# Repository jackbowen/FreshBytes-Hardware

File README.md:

# FreshBytes Hardware

All of the hardware needed to run FreshBytes, a hydroponic and aquaponic monitoring and control system. The system runs on [this software](https://github.com/jackbowen/FreshBytes-Backend) and is interacted with through [this app](https://github.com/jackbowen/FreshBytes-WebApp).

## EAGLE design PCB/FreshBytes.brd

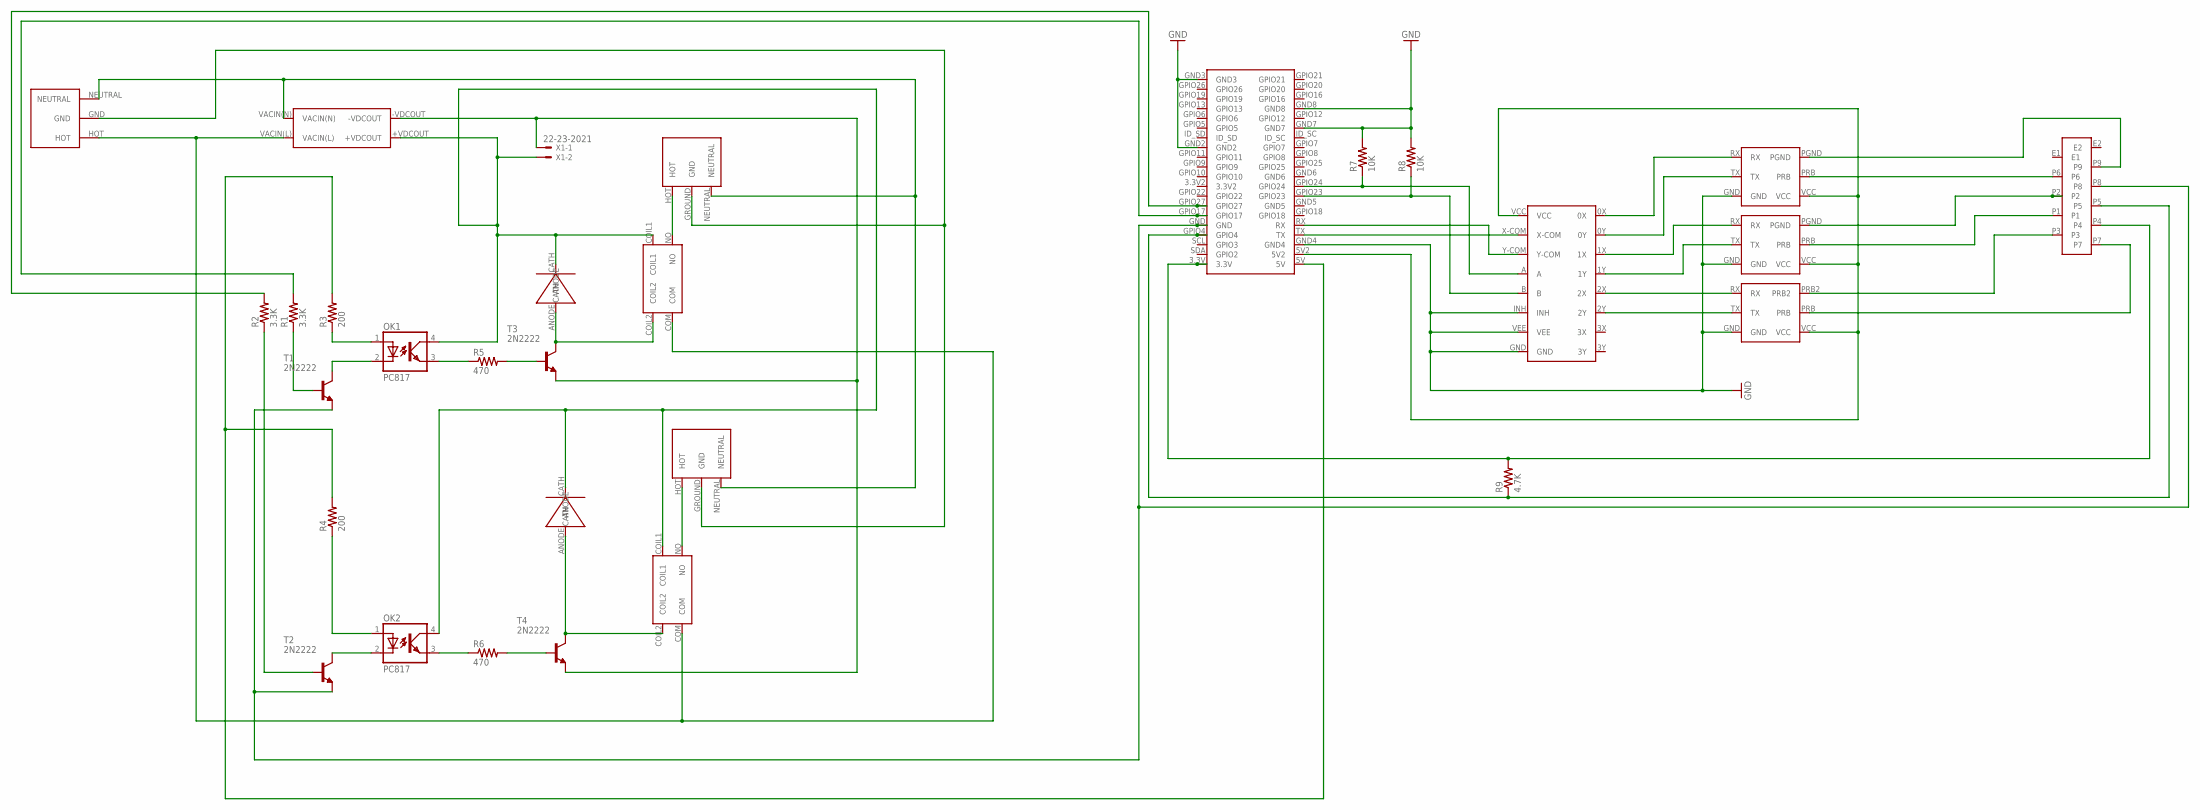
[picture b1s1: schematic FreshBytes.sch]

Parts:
MUX: 7HC4052_MUX; SSOP16
OK1, OK2: PC817; DIL04
R1, R2: 3.3K; R0805
R3, R4: 200; R0805
R5, R6: 470; R0805
R7, R8: 10K; R0805
R9: 4.7K; R0805
T1, T2, T3, T4: 2N2222; TO92-EBC-OVAL
U$1: POWER_IN
U$2, U$3: VTB8441BH
U$4: 9POS_MINI_DIN
U$5: ATLAS_DO_WITH_ICON
U$6, U$7: IEC_FEMALE
U$8: ATLAS_PH_WITH_ICON
U$9: ATLAS_PPM_WITH_ICON
U$10: RPI_ZERO
U$11, U$12: RELAY
U$17: RAC02-05SC_ACDCCONVERTER
X1: 22-23-2021

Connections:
3.3V2: U$10.3.3V2
AGND: T3.E, T4.E, U$17.-VDCOUT, X1.1
DGND: T1.E, T2.E, U$4.P8, U$10.GND
GND: MUX.GND, MUX.INH, MUX.VEE, R7.2, R8.2, U$5.GND, U$8.GND, U$9.GND, U$10.GND2, U$10.GND3, U$10.GND4, U$10.GND7, U$10.GND8
GND5: U$10.GND5
unnamed: R2.2, U$10.GPIO27
unnamed: R1.1, T1.B
unnamed: OK1.1 (A), R3.1
unnamed: OK1.2 (C), T1.C
unnamed: MUX.X-COM, U$10.TX
unnamed: R2.1, T2.B
unnamed: U$6.HOT, U$11.NO
unnamed: OK2.1 (A), R4.1
unnamed: OK2.2 (C), T2.C
unnamed: OK2.3 (EMIT), R6.1
unnamed: OK1.3 (EMIT), R5.1
unnamed: R5.2, T3.B
unnamed: R6.2, T4.B
unnamed: T4.C, U$3.ANODE, U$12.COIL2
unnamed: U$7.HOT, U$12.NO
unnamed: T3.C, U$2.ANODE, U$11.COIL2
unnamed: U$1.HOT, U$11.COM, U$12.COM, U$17.VACIN(L)
unnamed: U$1.NEUTRAL, U$6.NEUTRAL, U$7.NEUTRAL, U$17.VACIN(N)
unnamed: MUX.Y-COM, U$10.RX
unnamed: MUX.2Y, U$9.TX
unnamed: MUX.2X, U$9.RX
unnamed: MUX.1Y, U$8.TX
unnamed: MUX.1X, U$8.RX
unnamed: MUX.0Y, U$5.TX
unnamed: MUX.0X, U$5.RX
unnamed: MUX.A, R7.1, U$10.GPIO24
unnamed: U$4.P9, U$5.PGND
unnamed: OK1.4 (COL), OK2.4 (COL), U$2.CATH, U$3.CATH, U$11.COIL1, U$12.COIL1, U$17.+VDCOUT, X1.2
unnamed: MUX.VCC, U$5.VCC, U$8.VCC, U$9.VCC, U$10.5V2
unnamed: R1.2, U$10.GPIO17
unnamed: R9.2, U$4.P4, U$10.3.3V
unnamed: U$4.P7, U$9.PRB
unnamed: U$4.P3, U$9.PRB2
unnamed: U$4.P1, U$8.PRB
unnamed: U$4.P2, U$8.PGND
unnamed: U$4.P6, U$5.PRB
unnamed: R9.1, U$4.P5, U$10.GPIO4
unnamed: MUX.B, R8.1, U$10.GPIO23
unnamed: R3.2, R4.2, U$10.5V
PGND: U$1.GND, U$6.GROUND (GND), U$7.GROUND (GND)

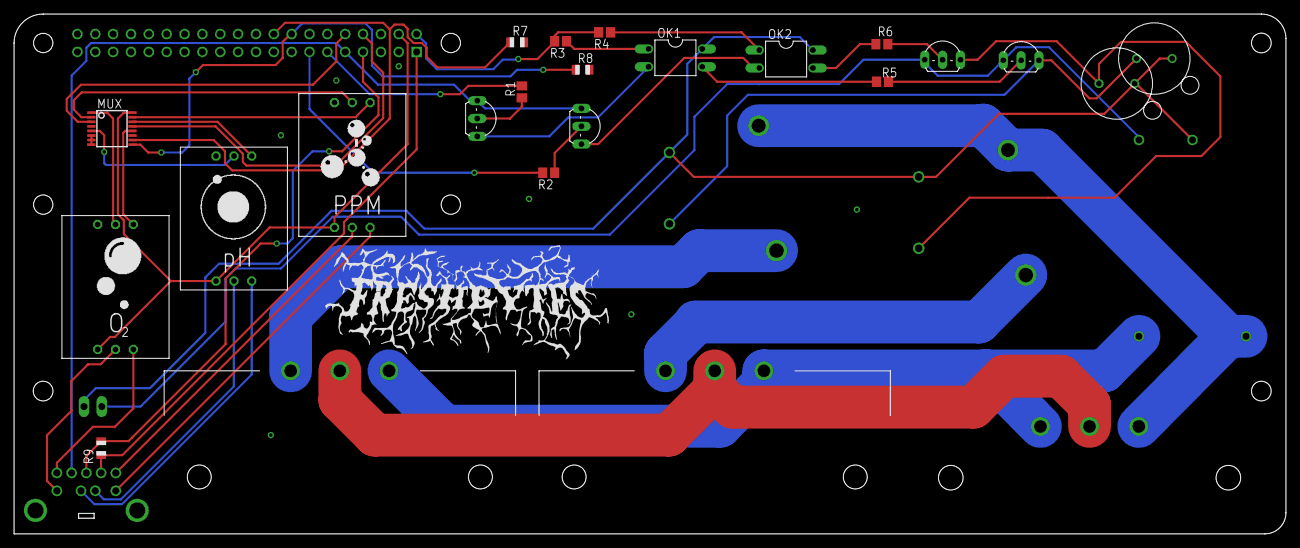
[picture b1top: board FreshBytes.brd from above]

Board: 2 copper layers, 181.0 x 74.0 mm, 30 parts (1 on the bottom side), 43 nets.

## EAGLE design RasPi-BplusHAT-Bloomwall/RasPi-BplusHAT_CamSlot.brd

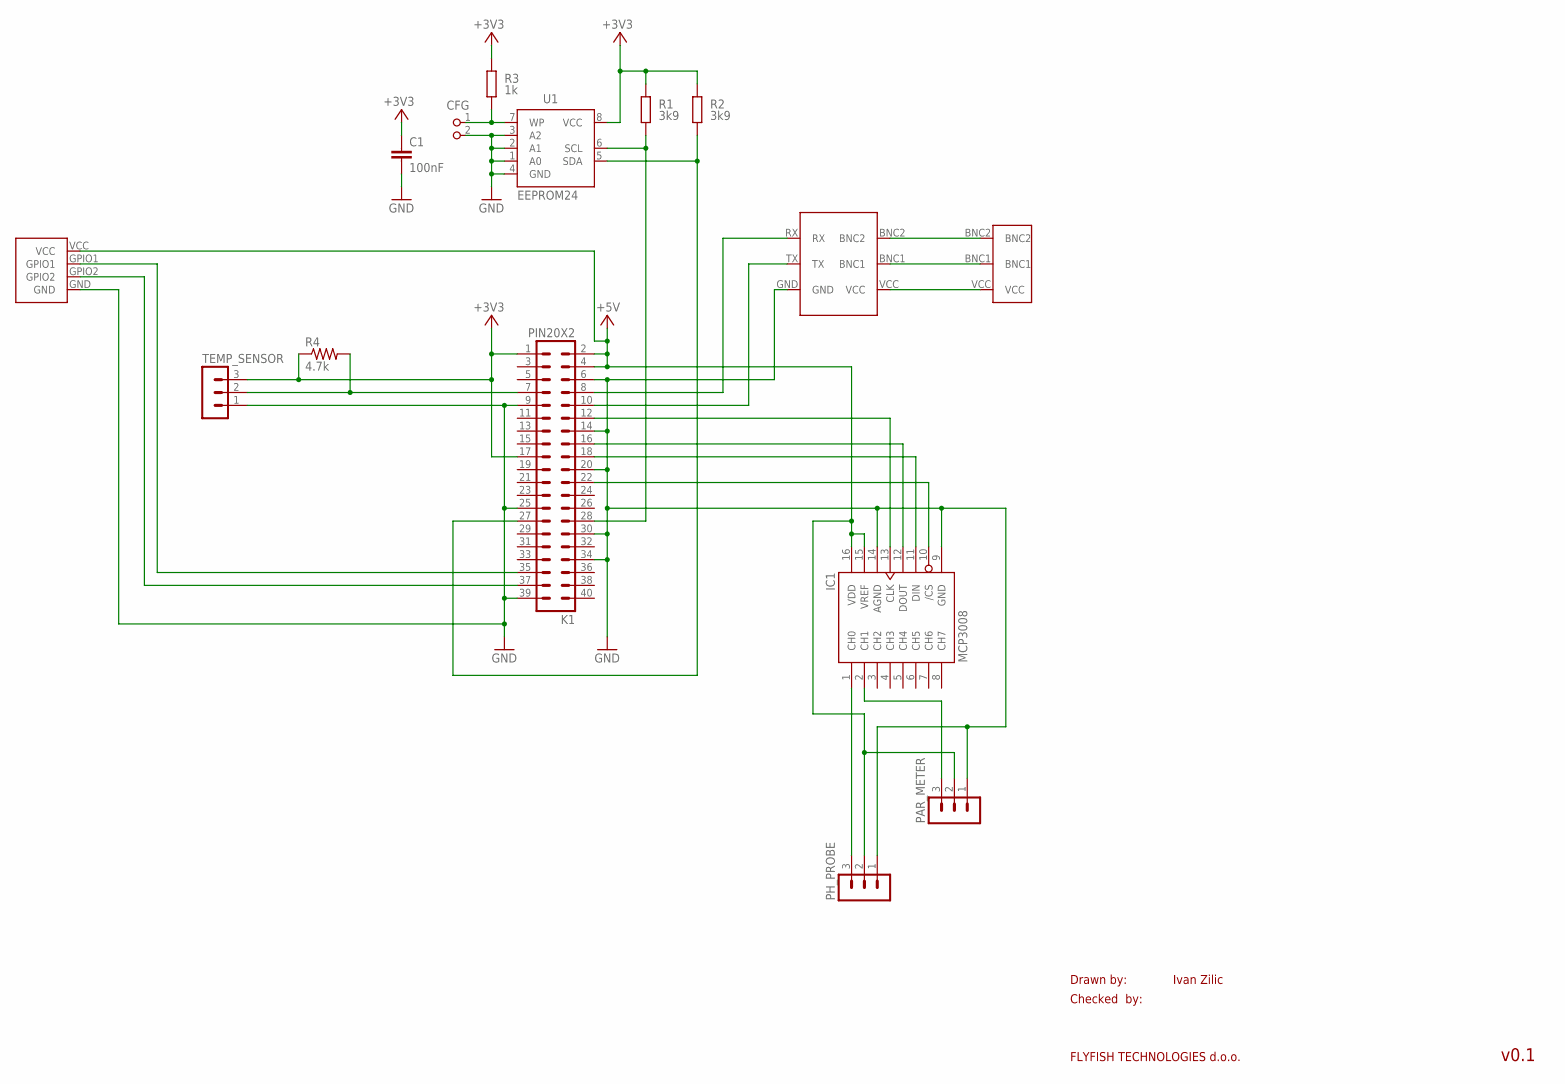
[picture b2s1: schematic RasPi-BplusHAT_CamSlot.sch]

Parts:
C1: 100nF; C0805K
CFG: PIN2_100; PIN_W_2
IC1: MCP3008; DIL16
K1: PIN20X2; PIN_20X2
PAR_METER: MA03-1
PH_PROBE: MA03-1
R1, R2: 3k9; M0805; TOLERANCE 5%
R3: 1k; M0805; TOLERANCE 5%
R4: 4.7k; R0805
TEMP_SENSOR: MA03-1
U1: EEPROM24; SOIC8
U$1: MTA-156; MTA-156_HEADER
U$2: ATLAS_EC_CIRCUIT
U$3: ATLAS_EC_PROBE

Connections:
+3V3: C1.1, K1.1, K1.17, R1.2, R2.2, R3.2, R4.1, TEMP_SENSOR.3, U1.8 (VCC)
+5V: IC1.15 (VREF), IC1.16 (VDD), K1.2, K1.4, PAR_METER.2, PH_PROBE.2, U$1.VCC
GND: C1.2, CFG.2, IC1.9 (GND), IC1.14 (AGND), K1.6, K1.9, K1.14, K1.20, K1.25, K1.30, K1.34, K1.39, PAR_METER.1, PH_PROBE.1, TEMP_SENSOR.1, U1.1 (A0), U1.2 (A1), U1.3 (A2), U1.4 (GND), U$1.GND, U$2.GND
unnamed: K1.28, R1.1, U1.6 (SCL)
unnamed: K1.27, R2.1, U1.5 (SDA)
unnamed: CFG.1, R3.1, U1.7 (WP)
unnamed: K1.7, R4.2, TEMP_SENSOR.2
unnamed: IC1.13 (CLK), K1.12
unnamed: IC1.12 (DOUT), K1.16
unnamed: IC1.11 (DIN), K1.18
unnamed: IC1.10 (/CS), K1.22
unnamed: IC1.1 (CH0), PH_PROBE.3
unnamed: U$2.BNC2, U$3.BNC2
unnamed: U$2.BNC1, U$3.BNC1
unnamed: U$2.VCC, U$3.VCC
unnamed: K1.8, U$2.RX
unnamed: K1.10, U$2.TX
unnamed: IC1.2 (CH1), PAR_METER.3
unnamed: K1.35, U$1.GPIO1
unnamed: K1.37, U$1.GPIO2

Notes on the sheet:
Drawn by:
Checked by:
FLYFISH TECHNOLOGIES d.o.o.
Ivan Zilic
v0.1

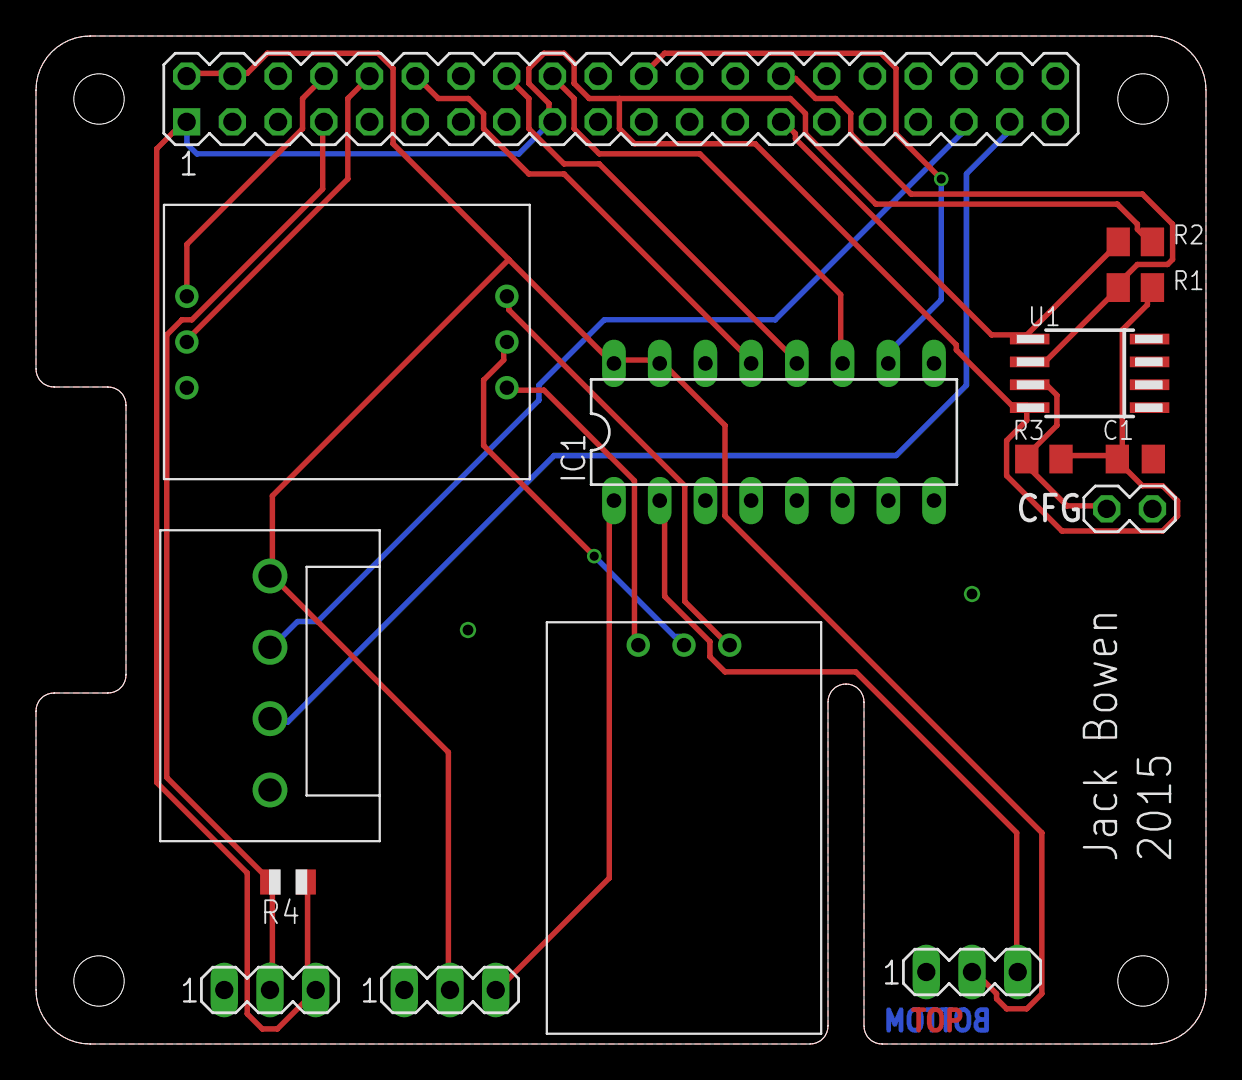
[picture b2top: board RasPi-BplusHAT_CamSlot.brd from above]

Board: 2 copper layers, 65.0 x 56.0 mm, 15 parts (0 on the bottom side), 20 nets.

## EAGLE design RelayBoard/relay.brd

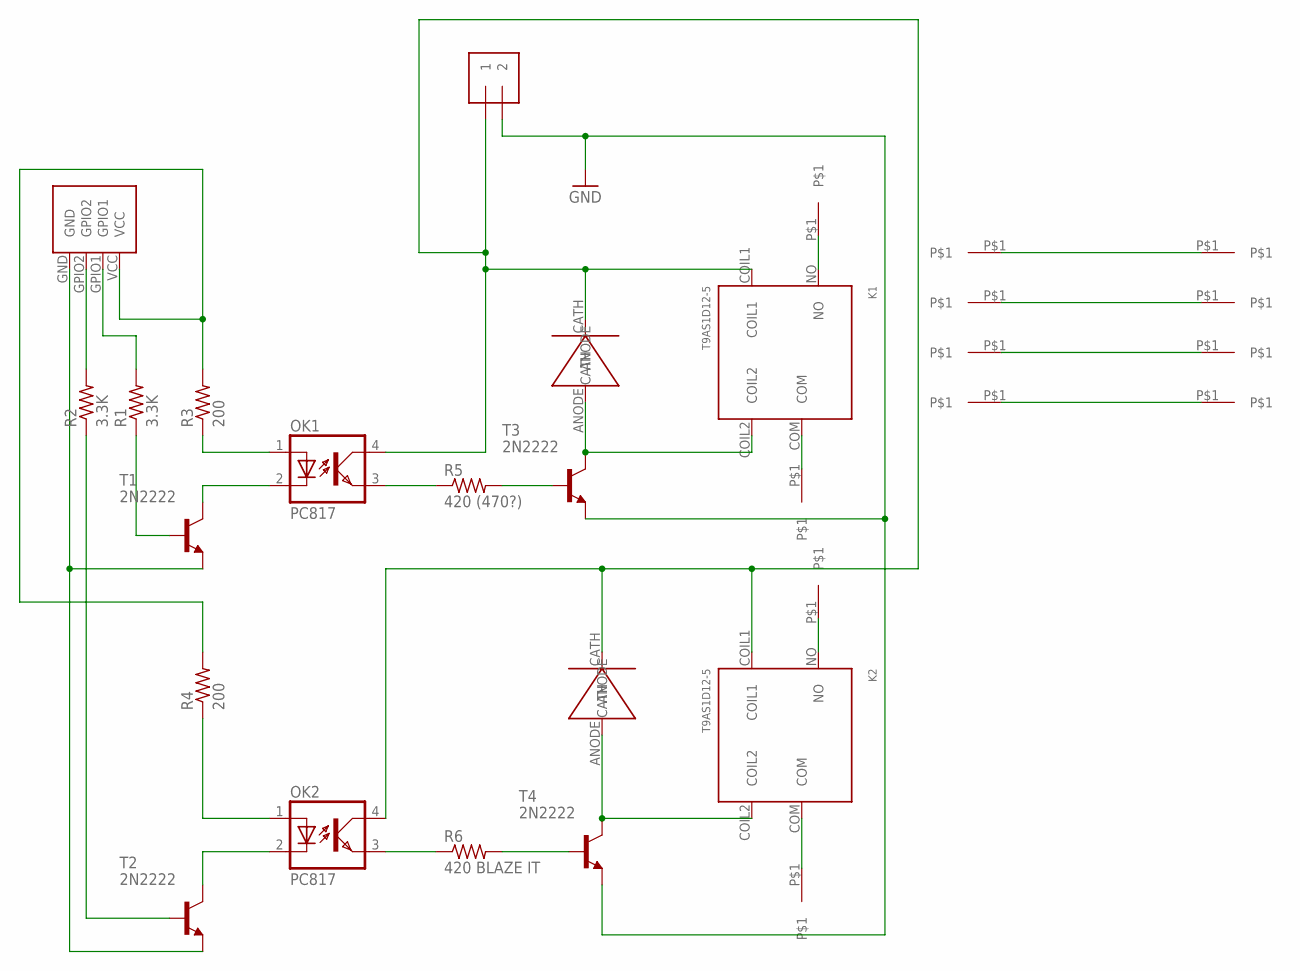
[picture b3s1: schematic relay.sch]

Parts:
J1: 1X2-3.5MM
K1, K2: T9AS1D12-5
OK1, OK2: PC817; DIL04
R1, R2: 3.3K; R0805
R3, R4: 200; R0805
R5: 420 (470?); R0805
R6: 420 BLAZE IT; R0805
T1, T2, T3, T4: 2N2222; TO92-EBC-OVAL
U$1: MTA-156; MTA-156_HEADER
U$2, U$3: VTB8441BH
U$4, U$5, U$6, U$7, U$8, U$9, U$10, U$11, U$12, U$13, U$14, U$15: MAIN

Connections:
GND: J1.2, T3.E, T4.E
unnamed: R2.2, U$1.GPIO2
unnamed: R1.2, U$1.GPIO1
unnamed: R1.1, T1.B
unnamed: OK1.1 (A), R3.1
unnamed: OK1.2 (C), T1.C
unnamed: R3.2, R4.2, U$1.VCC
unnamed: T1.E, T2.E, U$1.GND
unnamed: R2.1, T2.B
unnamed: OK2.1 (A), R4.1
unnamed: OK2.2 (C), T2.C
unnamed: OK2.3 (EMIT), R6.1
unnamed: OK1.3 (EMIT), R5.1
unnamed: R5.2, T3.B
unnamed: R6.2, T4.B
unnamed: K2.COIL2, T4.C, U$3.ANODE
unnamed: U$12.P$1, U$13.P$1
unnamed: K1.COIL2, T3.C, U$2.ANODE
unnamed: U$14.P$1, U$15.P$1
unnamed: K1.NO, U$4.P$1
unnamed: K1.COM, U$5.P$1
unnamed: J1.1, K1.COIL1, K2.COIL1, OK1.4 (COL), OK2.4 (COL), U$2.CATH, U$3.CATH
unnamed: K2.NO, U$6.P$1
unnamed: K2.COM, U$7.P$1
unnamed: U$9.P$1, U$11.P$1
unnamed: U$8.P$1, U$10.P$1

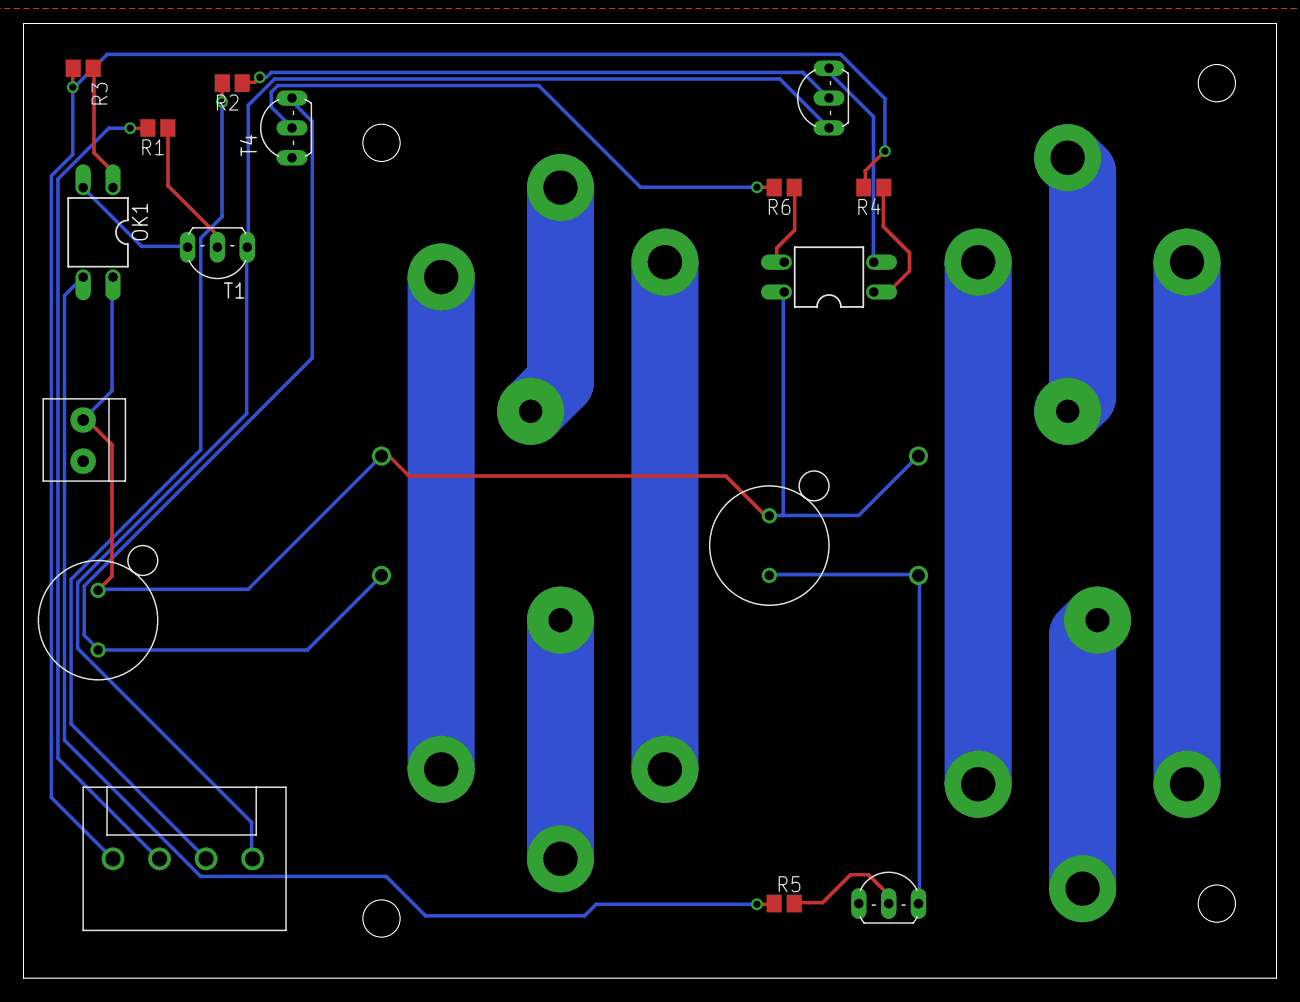
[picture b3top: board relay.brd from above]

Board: 2 copper layers, 106.7 x 81.3 mm, 30 parts (0 on the bottom side), 26 nets.

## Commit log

2017-05-10 finished schematic saved in Relayboard_2
2017-05-12 Starting to work on enclosure
2017-05-18 change power receptacles to thru hole
2017-05-18 added bill of materials and moved 9 pos connector to proper location on brd. 40 pin connector and 1 of the female power receptacles are also in the correct y position
2017-05-22 placed all components on board (not routed)
2017-05-23 routed ac. 3mm extension on male power receptacle
2017-05-25 flipped relays and repositioned power receptacles
2017-05-25 update enclosure drawing and add diodes to bill of materials
2017-05-31 Route everything. Add logo
2017-06-01 GND pour and add gerbers
2017-06-02 Reduced DPI of silkscreen to OSH Park can actually fabricate them. New gerbers.
2017-06-02 decrease pad size for main connection
2017-06-16 update bill of materials and enclosure drawing
2017-06-23 update enclosure drawing and add start of lid sketch
2017-07-04 update lid pde
2018-08-24 Swap to R Pi Zero W as the brains
    Power inlet may be in the wrong location. Will commit again tomorrow with proper spot.
2018-08-28 Fix component location in BRD
2018-08-29 Add logo to BRD file, create gerbers, update BOM
2018-08-30 Update CAD drawings
2018-09-19 Fix drill size for RPi headers. Swapping over to Rhino for CAD stuff
2018-09-21 Add 3d printable enclosure
2018-09-21 Edit axon view in Inkscape to adjust fill colors and line weights
2018-09-25 Start of exploded axon view
2021-01-18 Refine vector drawing
